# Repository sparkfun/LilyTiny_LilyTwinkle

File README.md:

LilyTiny / LilyTwinkle
======================

[  
*LilyTiny (DEV-10899)*](https://www.sparkfun.com/products/10899) / [*LilyTwinkle (DEV-11364)*](https://www.sparkfun.com/products/11364)

LilyTiny and LilyTwinkle are ATtiny85-based development boards for eTextiles applications. Due to the small size of the board and hardware limitations of the processor, they do not have a bootloader like a conventional LilyPad Arduino compatible does. Instead, six pads are available in the center of the back side of the board, allowing it to be reprogrammed with a standard AVR ISP programmer simply by inserting male headers into the end of the programming cable and pressing them against the board.

In order to write new code for the ATtiny you will need to add support to the Arduino IDE. Please refer to the High-Low Tech group at MIT for a great tutorial on doing this: [http://hlt.media.mit.edu/?p=1695](http://hlt.media.mit.edu/?p=1695)

Repository Contents
-------------------

* **/Firmware** - Separate firmware files for the LilyTiny and the LilyTwinkle.
* **/Fritzing** - Fritzing Example wiring images
* **/Hardware** - All hardware files for both the LilyTiny *and* the LilyTwinkle (they are identical boards). For simplicity's sake, the hardware files are named *LilyTiny*.
* **/Production** - Test bed files and production panel files

Documentation
--------------

* Getting Started Tutorials
  * **[LDK Experiment 6: Microcontroller Circuits](https://learn.sparkfun.com/tutorials/ldk-experiment-6-microcontroller-circuits)**
  * **[Using the LilyPad LilyTwinkle board](https://www.sparkfun.com/tutorials/390)**
* Project Tutorials
  * **[Twinkle Zodiac Constellation](https://learn.sparkfun.com/tutorials/twinkle-zodiac-constellation)**
  * **[Night Sky Halloween Costume](https://learn.sparkfun.com/tutorials/night-sky-halloween-costume)**
  * **[Firefly Jar Assembly Guide](https://learn.sparkfun.com/tutorials/firefly-jar-assembly-guide)** 
  * **[Soft Circuits: LED Feelings Pizza](https://learn.sparkfun.com/tutorials/soft-circuits-led-feelings-pizza)**
  * **[Twinkling Trick or Treat Bag](https://learn.sparkfun.com/tutorials/twinkling-trick-or-treat-bag)**
  * **[Light Up Pennant with E-Textiles](https://learn.sparkfun.com/tutorials/light-up-pennant-with-e-textiles)**
  * **[LilyTiny Plush Monster](https://learn.sparkfun.com/tutorials/lilytiny-plush-monster)**
  * **[Twinkling Fairy Wings](https://www.sparkfun.com/tutorials/396)**
* **[Tiny AVR Programmer Hookup Guide](https://learn.sparkfun.com/tutorials/tiny-avr-programmer-hookup-guide)** - Hookup guide to reprogram an ATtiny85.
* **[Re-Programming the LilyTiny / LilyTwinkle](https://learn.sparkfun.com/tutorials/re-programming-the-lilytiny--lilytwinkle)** - Tutorial to reprogram the LilyTiny or LilyTwinkle.
* **[Quick Reference Guide for ATTiny85](https://learn.sparkfun.com/resources/96)** 

License Information
-------------------
The hardware is released under [Creative Commons ShareAlike 4.0 International](https://creativecommons.org/licenses/by-sa/4.0/).
The code is beerware; if you see me (or any other SparkFun employee) at the local, and you've found our code helpful, please buy us a round!

Distributed as-is; no warranty is given.

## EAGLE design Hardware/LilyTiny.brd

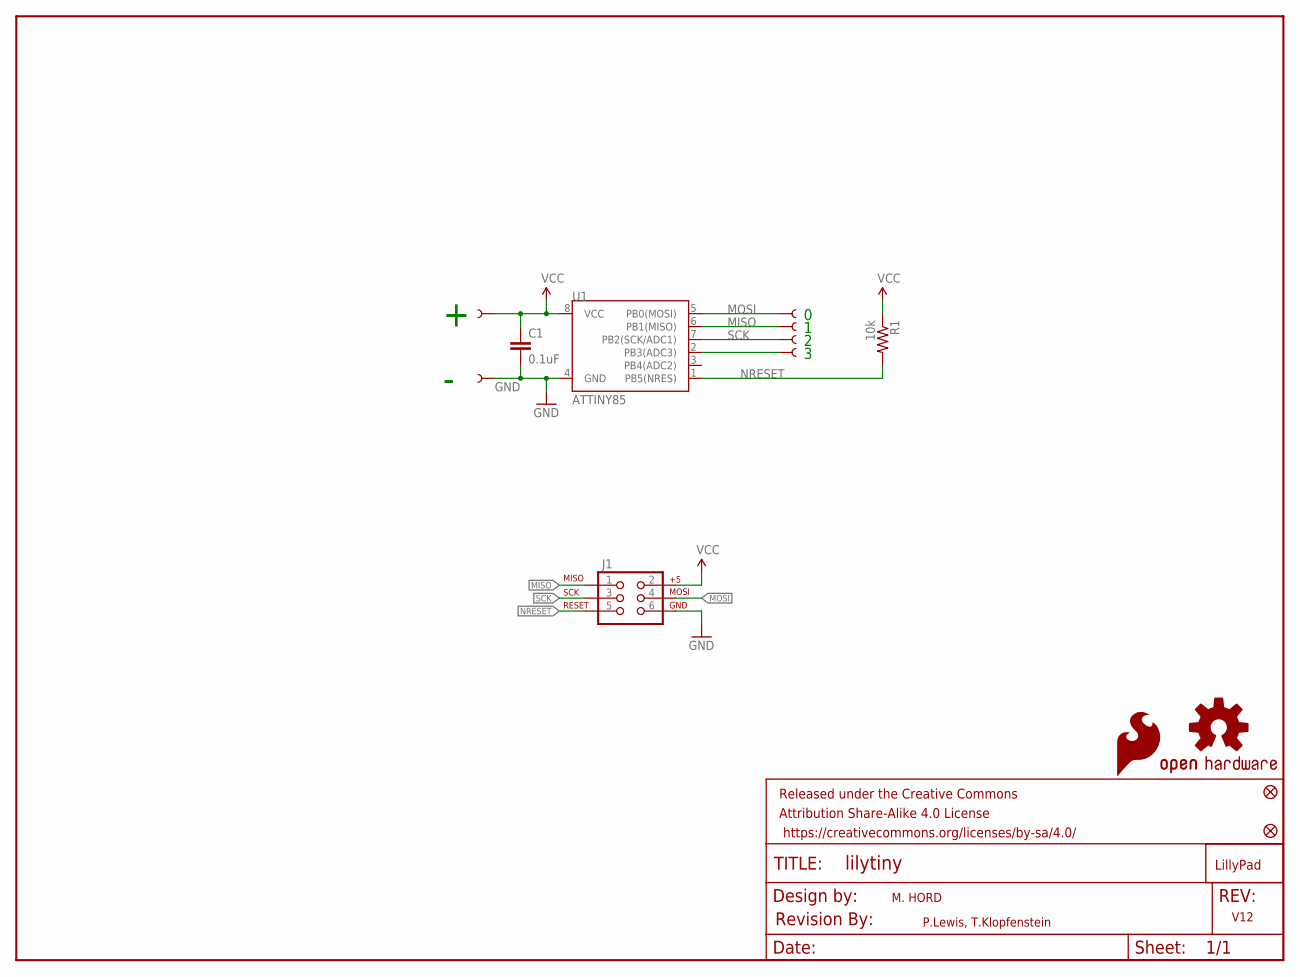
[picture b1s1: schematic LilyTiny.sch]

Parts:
C1: 0.1uF; 0603-CAP
FID1, FID2: FIDUCIAL1X2; FIDUCIAL-1X2
FRAME2: FRAME-LETTER; CREATIVE_COMMONS
J1: AVR_SPI_PRG_6TESTPOINTS; 2X3_TEST_POINTS
LOGO1: OSHW-LOGOS; OSHW-LOGO-S
LOGO2: SFE_LOGO_FLAME.1_INCH; SFE_LOGO_FLAME_.1
R1: 10k; 0603-RES
U1: ATTINY85; SO08-EIAJ
U$1: REVISION
U$2, U$3, U$4, U$5, U$6, U$7: SEWTAP6; PETAL-SMALL-2SIDE
U$8: LOGO-LPL; LOGO-L

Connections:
GND: C1.2, J1.6, U1.4 (GND), U$2.1
MISO: J1.1, U1.6 (PB1(MISO)), U$3.1
MOSI: J1.4, U1.5 (PB0(MOSI)), U$7.1
unnamed: U1.2 (PB3(ADC3)), U$6.1
NRESET: J1.5, R1.2, U1.1 (PB5(NRES))
SCK: J1.3, U1.7 (PB2(SCK/ADC1)), U$4.1
VCC: C1.1, J1.2, R1.1, U1.8 (VCC), U$5.1

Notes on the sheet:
M. HORD
P.Lewis, T.Klopfenstein
V12

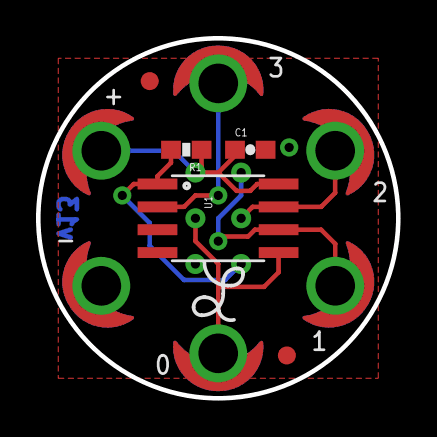
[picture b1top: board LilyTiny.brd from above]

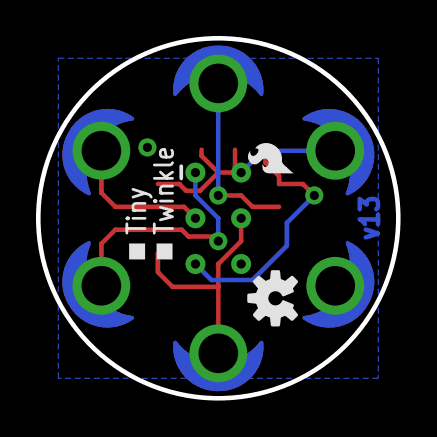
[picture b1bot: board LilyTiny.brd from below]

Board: 2 copper layers, 20.0 x 20.0 mm, 17 parts (3 on the bottom side), 7 nets.

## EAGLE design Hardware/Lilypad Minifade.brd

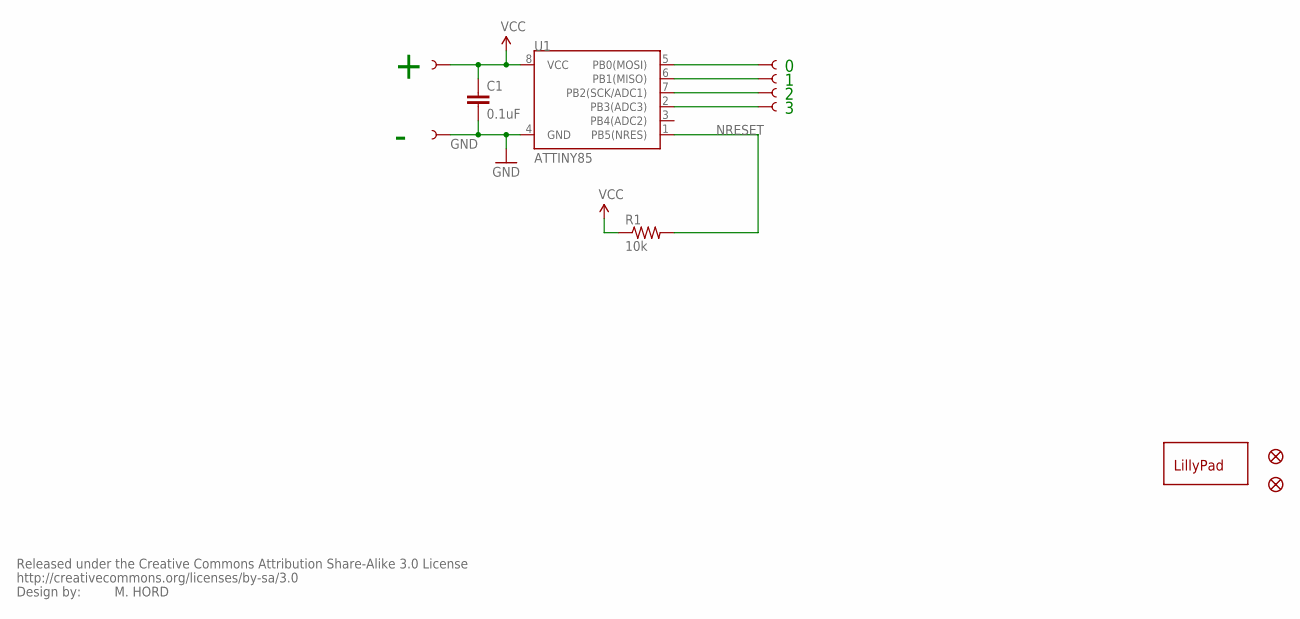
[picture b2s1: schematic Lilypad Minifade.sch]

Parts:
C1: 0.1uF; 0402-CAP
JP1, JP2: FIDUCIALUFIDUCIAL; MICRO-FIDUCIAL
R1: 10k; 0402-RES
U1: ATTINY85; SO08-EIAJ
U$1: CREATIVE_COMMONS
U$2, U$3, U$4, U$5, U$6, U$7: SEWTAP6; PETAL-SMALL-2SIDE
U$8: LOGO-LPL; LOGO-L

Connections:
GND: C1.2, U1.4 (GND), U$2.1
unnamed: U1.5 (PB0(MOSI)), U$7.1
unnamed: U1.6 (PB1(MISO)), U$3.1
unnamed: U1.7 (PB2(SCK/ADC1)), U$4.1
unnamed: U1.2 (PB3(ADC3)), U$6.1
NRESET: R1.2, U1.1 (PB5(NRES))
VCC: C1.1, R1.1, U1.8 (VCC), U$5.1

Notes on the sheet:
M. HORD

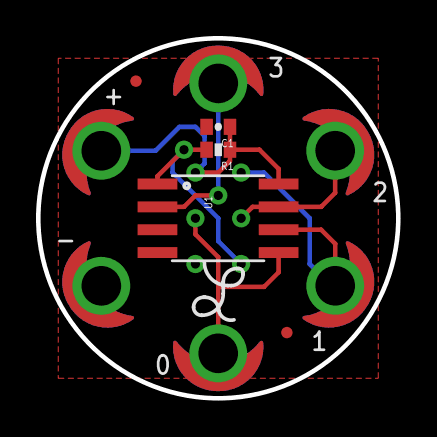
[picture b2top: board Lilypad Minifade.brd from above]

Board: 2 copper layers, 20.0 x 20.0 mm, 13 parts (0 on the bottom side), 7 nets.

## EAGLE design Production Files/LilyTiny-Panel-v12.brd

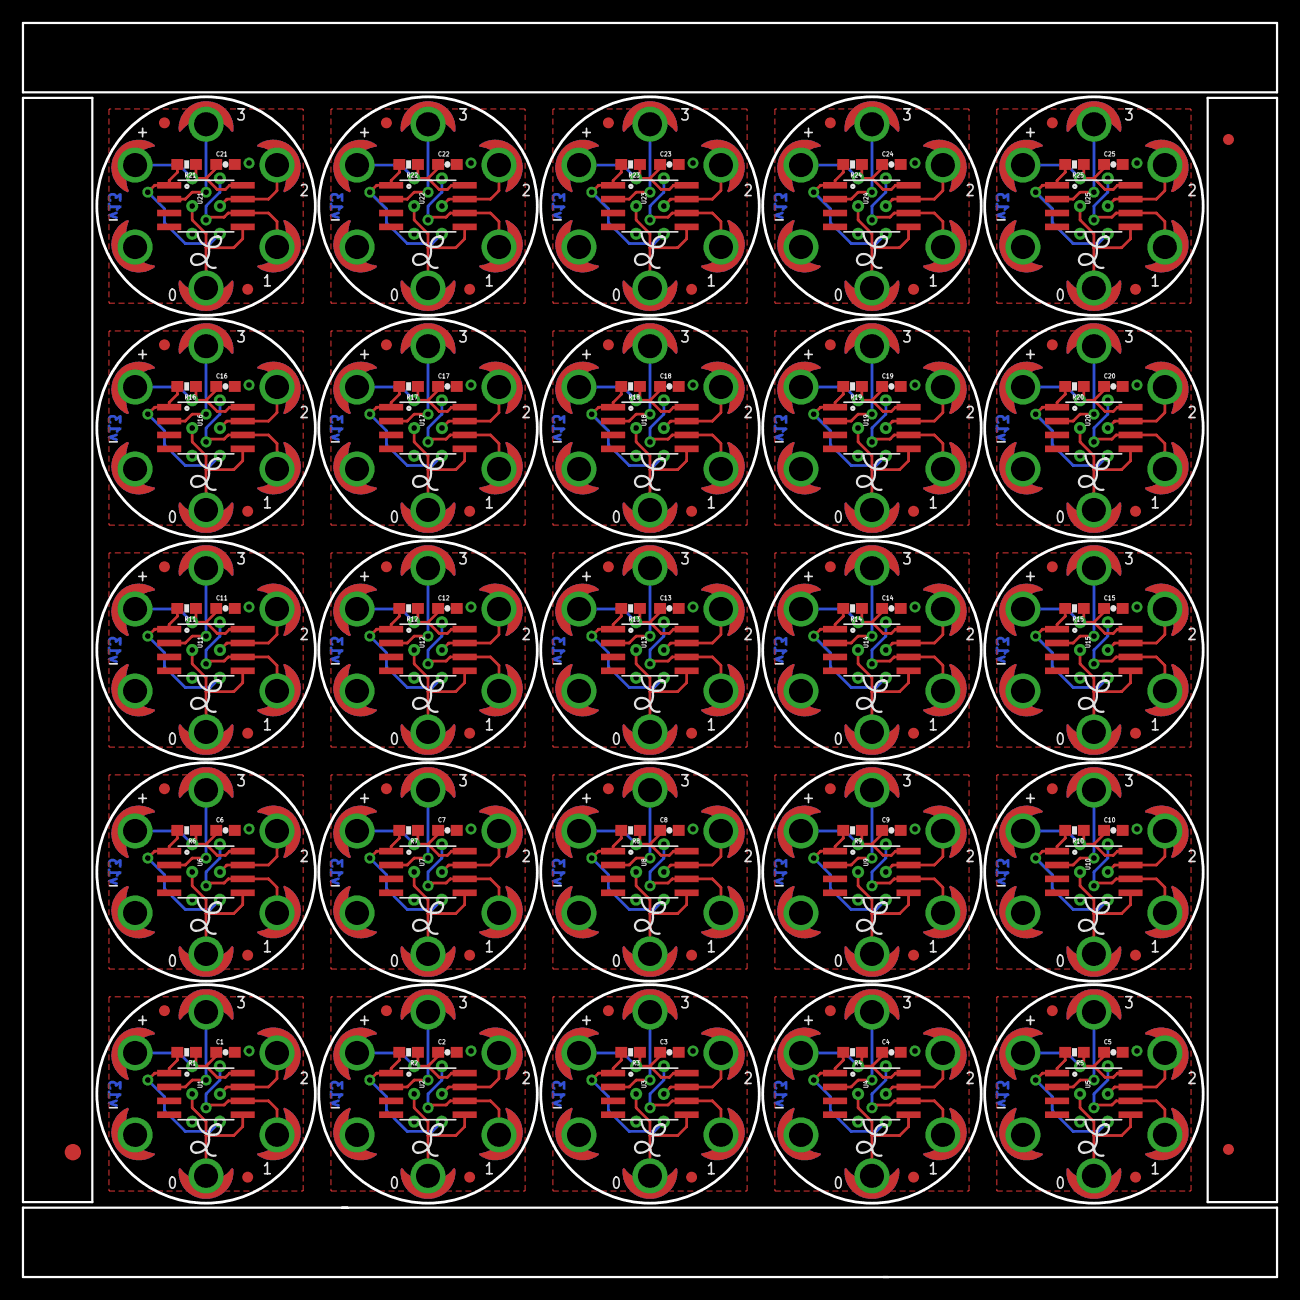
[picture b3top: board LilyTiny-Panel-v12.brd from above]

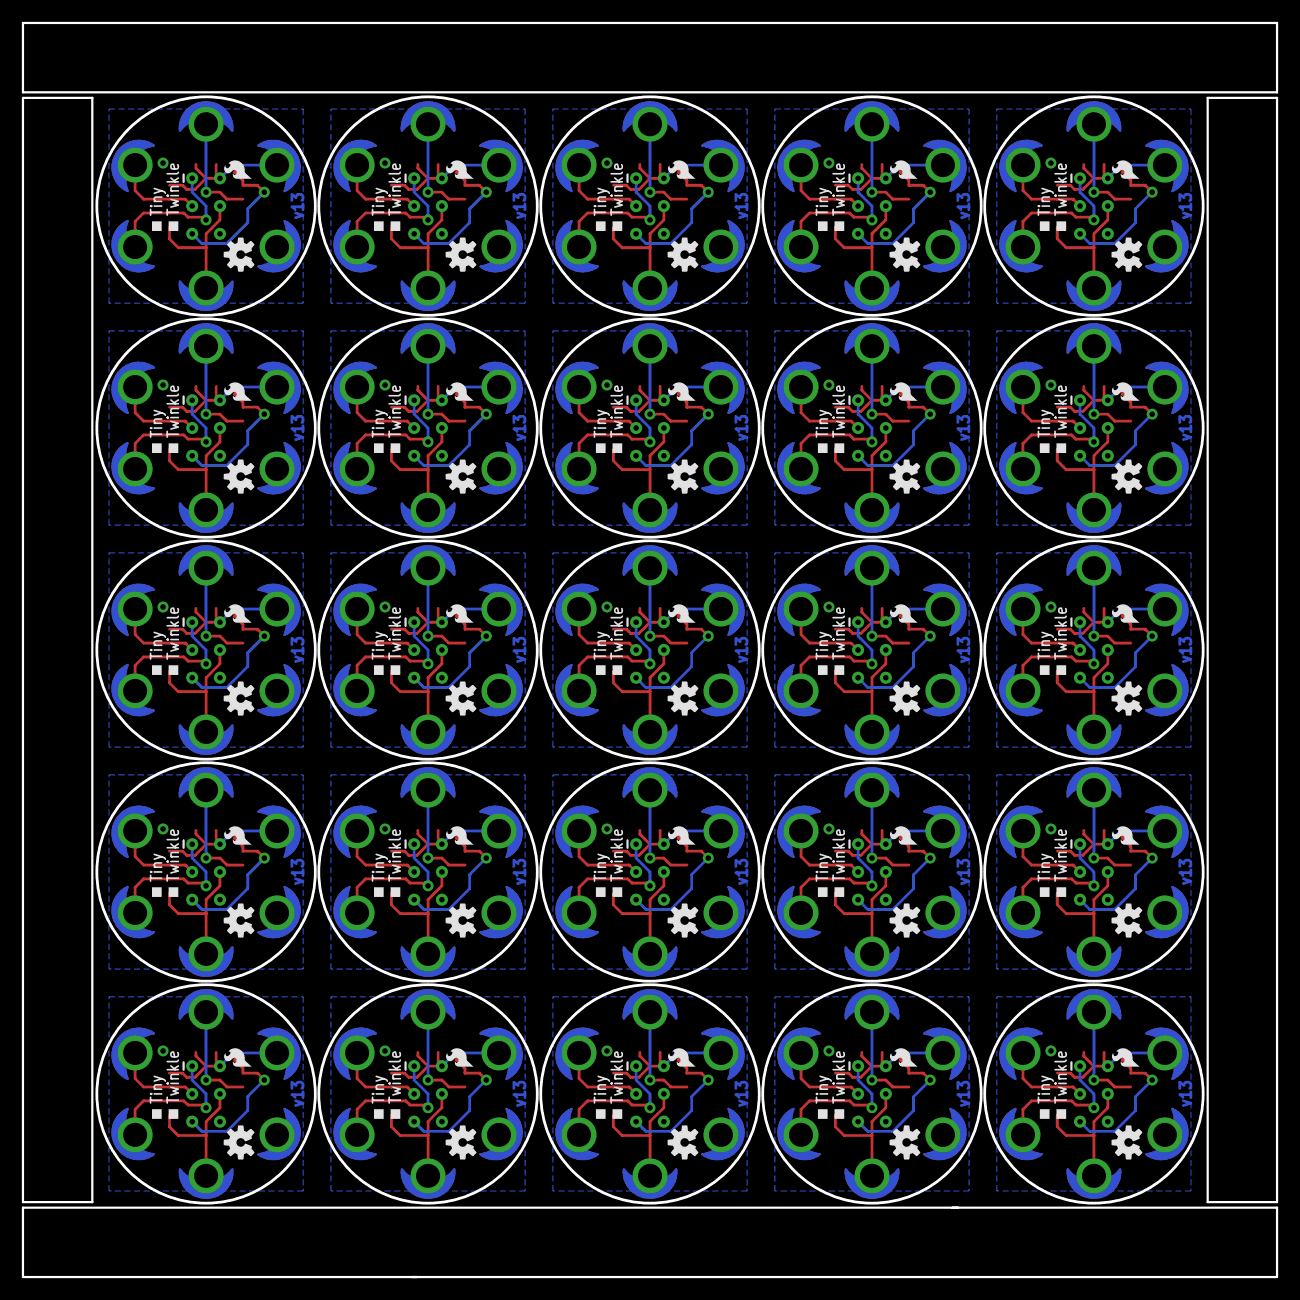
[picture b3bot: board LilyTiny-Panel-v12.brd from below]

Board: 2 copper layers, 114.8 x 114.8 mm, 378 parts (75 on the bottom side), 175 nets.

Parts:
C1, C2, C3, C4, C5, C6, C7, C8, C9, C10, C11, C12, C13, C14, C15, C16, C17, C18, C19, C20, C21, C22, C23, C24, C25: 0.1uF; 0603-CAP
E$1: FIDUCIAL-1.5X3
E$4, E$6: FIDUCIAL-1X2
FID1, FID2, FID3, FID4, FID5, FID6, FID7, FID8, FID9, FID10, FID11, FID12, FID13, FID14, FID15, FID16, FID17, FID18, FID19, FID20, FID21, FID22, FID23, FID24, FID25, FID26, FID27, FID28, FID29, FID30, FID31, FID32, FID33, FID34, FID35, FID36, FID37, FID38, FID39, FID40, FID41, FID42, FID43, FID44, FID45, FID46, FID47, FID48, FID49, FID50: FIDUCIAL1X2; FIDUCIAL-1X2
J1, J2, J3, J4, J5, J6, J7, J8, J9, J10, J11, J12, J13, J14, J15, J16, J17, J18, J19, J20, J21, J22, J23, J24, J25: 2X3_TEST_POINTS
LOGO1, LOGO3, LOGO5, LOGO7, LOGO9, LOGO11, LOGO13, LOGO15, LOGO17, LOGO19, LOGO21, LOGO23, LOGO25, LOGO27, LOGO29, LOGO31, LOGO33, LOGO35, LOGO37, LOGO39, LOGO41, LOGO43, LOGO45, LOGO47, LOGO49: OSHW-LOGOS; OSHW-LOGO-S
LOGO2, LOGO4, LOGO6, LOGO8, LOGO10, LOGO12, LOGO14, LOGO16, LOGO18, LOGO20, LOGO22, LOGO24, LOGO26, LOGO28, LOGO30, LOGO32, LOGO34, LOGO36, LOGO38, LOGO40, LOGO42, LOGO44, LOGO46, LOGO48, LOGO50: SFE_LOGO_FLAME.1_INCH; SFE_LOGO_FLAME_.1
R1, R2, R3, R4, R5, R6, R7, R8, R9, R10, R11, R12, R13, R14, R15, R16, R17, R18, R19, R20, R21, R22, R23, R24, R25: 10k; 0603-RES
U1, U2, U3, U4, U5, U6, U7, U8, U9, U10, U11, U12, U13, U14, U15, U16, U17, U18, U19, U20, U21, U22, U23, U24, U25: ATTINY85; SO08-EIAJ
U$1, U$2, U$3, U$4, U$5, U$6, U$7, U$9, U$10, U$11, U$12, U$13, U$15, U$16, U$17, U$18, U$19, U$20, U$22, U$23, U$24, U$25, U$26, U$27, U$29, U$30, U$31, U$32, U$33, U$34, U$36, U$37, U$38, U$39, U$40, U$41, U$43, U$44, U$45, U$46, U$47, U$48, U$50, U$51, U$52, U$53, U$54, U$55, U$57, U$58, U$59, U$60, U$61, U$62, U$64, U$65, U$66, U$67, U$68, U$69, U$71, U$72, U$73, U$74, U$75, U$76, U$78, U$79, U$80, U$81, U$82, U$83, U$85, U$86, U$87, U$88, U$89, U$90, U$92, U$93, U$94, U$95, U$96, U$97, U$99, U$100, U$101, U$102, U$103, U$104, U$106, U$107, U$108, U$109, U$110, U$111, U$113, U$114, U$115, U$116, U$117, U$118, U$120, U$121, U$122, U$123, U$124, U$125, U$127, U$128, U$129, U$130, U$131, U$132, U$134, U$135, U$136, U$137, U$138, U$139, U$141, U$142, U$143, U$144, U$145, U$146, U$148, U$149, U$150, U$151, U$152, U$153, U$155, U$156, U$157, U$158, U$159, U$160, U$162, U$163, U$164, U$165, U$166, U$167, U$169, U$170, U$171, U$172, U$173, U$174: SEWTAP6; PETAL-SMALL-2SIDE
U$8, U$14, U$21, U$28, U$35, U$42, U$49, U$56, U$63, U$70, U$77, U$84, U$91, U$98, U$105, U$112, U$119, U$126, U$133, U$140, U$147, U$154, U$161, U$168, U$175: LOGO-LPL; LOGO-L

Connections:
GND: C1.2, J1.6, U1.4, U$2.1
GND1: C2.2, J2.6, U2.4, U$1.1
GND2: C3.2, J3.6, U3.4, U$15.1
GND3: C4.2, J4.6, U4.4, U$22.1
GND4: C5.2, J5.6, U5.4, U$29.1
GND5: C6.2, J6.6, U6.4, U$36.1
GND6: C7.2, J7.6, U7.4, U$43.1
GND7: C8.2, J8.6, U8.4, U$50.1
GND8: C9.2, J9.6, U9.4, U$57.1
GND9: C10.2, J10.6, U10.4, U$64.1
GND10: C11.2, J11.6, U11.4, U$71.1
GND11: C12.2, J12.6, U12.4, U$78.1
GND12: C13.2, J13.6, U13.4, U$85.1
GND13: C14.2, J14.6, U14.4, U$92.1
GND14: C15.2, J15.6, U15.4, U$99.1
GND15: C16.2, J16.6, U16.4, U$106.1
GND16: C17.2, J17.6, U17.4, U$113.1
GND17: C18.2, J18.6, U18.4, U$120.1
GND18: C19.2, J19.6, U19.4, U$127.1
GND19: C20.2, J20.6, U20.4, U$134.1
GND20: C21.2, J21.6, U21.4, U$141.1
GND21: C22.2, J22.6, U22.4, U$148.1
GND22: C23.2, J23.6, U23.4, U$155.1
GND23: C24.2, J24.6, U24.4, U$162.1
GND24: C25.2, J25.6, U25.4, U$169.1
MISO: J1.1, U1.6, U$3.1
MISO1: J2.1, U2.6, U$9.1
MISO2: J3.1, U3.6, U$16.1
MISO3: J4.1, U4.6, U$23.1
MISO4: J5.1, U5.6, U$30.1
MISO5: J6.1, U6.6, U$37.1
MISO6: J7.1, U7.6, U$44.1
MISO7: J8.1, U8.6, U$51.1
MISO8: J9.1, U9.6, U$58.1
MISO9: J10.1, U10.6, U$65.1
MISO10: J11.1, U11.6, U$72.1
MISO11: J12.1, U12.6, U$79.1
MISO12: J13.1, U13.6, U$86.1
MISO13: J14.1, U14.6, U$93.1
MISO14: J15.1, U15.6, U$100.1
MISO15: J16.1, U16.6, U$107.1
MISO16: J17.1, U17.6, U$114.1
MISO17: J18.1, U18.6, U$121.1
MISO18: J19.1, U19.6, U$128.1
MISO19: J20.1, U20.6, U$135.1
MISO20: J21.1, U21.6, U$142.1
MISO21: J22.1, U22.6, U$149.1
MISO22: J23.1, U23.6, U$156.1
MISO23: J24.1, U24.6, U$163.1
MISO24: J25.1, U25.6, U$170.1
MOSI: J1.4, U1.5, U$7.1
MOSI1: J2.4, U2.5, U$13.1
MOSI2: J3.4, U3.5, U$20.1
MOSI3: J4.4, U4.5, U$27.1
MOSI4: J5.4, U5.5, U$34.1
MOSI5: J6.4, U6.5, U$41.1
MOSI6: J7.4, U7.5, U$48.1
MOSI7: J8.4, U8.5, U$55.1
MOSI8: J9.4, U9.5, U$62.1
MOSI9: J10.4, U10.5, U$69.1
MOSI10: J11.4, U11.5, U$76.1
MOSI11: J12.4, U12.5, U$83.1
MOSI12: J13.4, U13.5, U$90.1
MOSI13: J14.4, U14.5, U$97.1
MOSI14: J15.4, U15.5, U$104.1
MOSI15: J16.4, U16.5, U$111.1
MOSI16: J17.4, U17.5, U$118.1
MOSI17: J18.4, U18.5, U$125.1
MOSI18: J19.4, U19.5, U$132.1
MOSI19: J20.4, U20.5, U$139.1
MOSI20: J21.4, U21.5, U$146.1
MOSI21: J22.4, U22.5, U$153.1
MOSI22: J23.4, U23.5, U$160.1
MOSI23: J24.4, U24.5, U$167.1
MOSI24: J25.4, U25.5, U$174.1
unnamed: U2.2, U$12.1
unnamed: U3.2, U$19.1
unnamed: U4.2, U$26.1
unnamed: U5.2, U$33.1
unnamed: U1.2, U$6.1
unnamed: U6.2, U$40.1
unnamed: U7.2, U$47.1
unnamed: U8.2, U$54.1
unnamed: U9.2, U$61.1
unnamed: U10.2, U$68.1
unnamed: U11.2, U$75.1
unnamed: U12.2, U$82.1
unnamed: U13.2, U$89.1
unnamed: U14.2, U$96.1
unnamed: U15.2, U$103.1
unnamed: U16.2, U$110.1
unnamed: U17.2, U$117.1
unnamed: U18.2, U$124.1
unnamed: U19.2, U$131.1
unnamed: U20.2, U$138.1
unnamed: U21.2, U$145.1
unnamed: U22.2, U$152.1
unnamed: U23.2, U$159.1
unnamed: U24.2, U$166.1
unnamed: U25.2, U$173.1
NRESET: J1.5, R1.2, U1.1
NRESET1: J2.5, R2.2, U2.1
NRESET2: J3.5, R3.2, U3.1
NRESET3: J4.5, R4.2, U4.1
NRESET4: J5.5, R5.2, U5.1
NRESET5: J6.5, R6.2, U6.1
NRESET6: J7.5, R7.2, U7.1
NRESET7: J8.5, R8.2, U8.1
NRESET8: J9.5, R9.2, U9.1
NRESET9: J10.5, R10.2, U10.1
NRESET10: J11.5, R11.2, U11.1
NRESET11: J12.5, R12.2, U12.1
NRESET12: J13.5, R13.2, U13.1
NRESET13: J14.5, R14.2, U14.1
NRESET14: J15.5, R15.2, U15.1
NRESET15: J16.5, R16.2, U16.1
NRESET16: J17.5, R17.2, U17.1
NRESET17: J18.5, R18.2, U18.1
NRESET18: J19.5, R19.2, U19.1
NRESET19: J20.5, R20.2, U20.1
NRESET20: J21.5, R21.2, U21.1
NRESET21: J22.5, R22.2, U22.1
NRESET22: J23.5, R23.2, U23.1
NRESET23: J24.5, R24.2, U24.1
NRESET24: J25.5, R25.2, U25.1
SCK: J1.3, U1.7, U$4.1
SCK1: J2.3, U2.7, U$10.1
SCK2: J3.3, U3.7, U$17.1
SCK3: J4.3, U4.7, U$24.1
SCK4: J5.3, U5.7, U$31.1
SCK5: J6.3, U6.7, U$38.1
SCK6: J7.3, U7.7, U$45.1
SCK7: J8.3, U8.7, U$52.1
SCK8: J9.3, U9.7, U$59.1
SCK9: J10.3, U10.7, U$66.1
SCK10: J11.3, U11.7, U$73.1
SCK11: J12.3, U12.7, U$80.1
SCK12: J13.3, U13.7, U$87.1
SCK13: J14.3, U14.7, U$94.1
SCK14: J15.3, U15.7, U$101.1
SCK15: J16.3, U16.7, U$108.1
SCK16: J17.3, U17.7, U$115.1
SCK17: J18.3, U18.7, U$122.1
SCK18: J19.3, U19.7, U$129.1
SCK19: J20.3, U20.7, U$136.1
SCK20: J21.3, U21.7, U$143.1
SCK21: J22.3, U22.7, U$150.1
SCK22: J23.3, U23.7, U$157.1
SCK23: J24.3, U24.7, U$164.1
SCK24: J25.3, U25.7, U$171.1
VCC: C1.1, J1.2, R1.1, U1.8, U$5.1
VCC1: C2.1, J2.2, R2.1, U2.8, U$11.1
VCC2: C3.1, J3.2, R3.1, U3.8, U$18.1
VCC3: C4.1, J4.2, R4.1, U4.8, U$25.1
VCC4: C5.1, J5.2, R5.1, U5.8, U$32.1
VCC5: C6.1, J6.2, R6.1, U6.8, U$39.1
VCC6: C7.1, J7.2, R7.1, U7.8, U$46.1
VCC7: C8.1, J8.2, R8.1, U8.8, U$53.1
VCC8: C9.1, J9.2, R9.1, U9.8, U$60.1
VCC9: C10.1, J10.2, R10.1, U10.8, U$67.1
VCC10: C11.1, J11.2, R11.1, U11.8, U$74.1
VCC11: C12.1, J12.2, R12.1, U12.8, U$81.1
VCC12: C13.1, J13.2, R13.1, U13.8, U$88.1
VCC13: C14.1, J14.2, R14.1, U14.8, U$95.1
VCC14: C15.1, J15.2, R15.1, U15.8, U$102.1
VCC15: C16.1, J16.2, R16.1, U16.8, U$109.1
VCC16: C17.1, J17.2, R17.1, U17.8, U$116.1
VCC17: C18.1, J18.2, R18.1, U18.8, U$123.1
VCC18: C19.1, J19.2, R19.1, U19.8, U$130.1
VCC19: C20.1, J20.2, R20.1, U20.8, U$137.1
VCC20: C21.1, J21.2, R21.1, U21.8, U$144.1
VCC21: C22.1, J22.2, R22.1, U22.8, U$151.1
VCC22: C23.1, J23.2, R23.1, U23.8, U$158.1
VCC23: C24.1, J24.2, R24.1, U24.8, U$165.1
VCC24: C25.1, J25.2, R25.1, U25.8, U$172.1

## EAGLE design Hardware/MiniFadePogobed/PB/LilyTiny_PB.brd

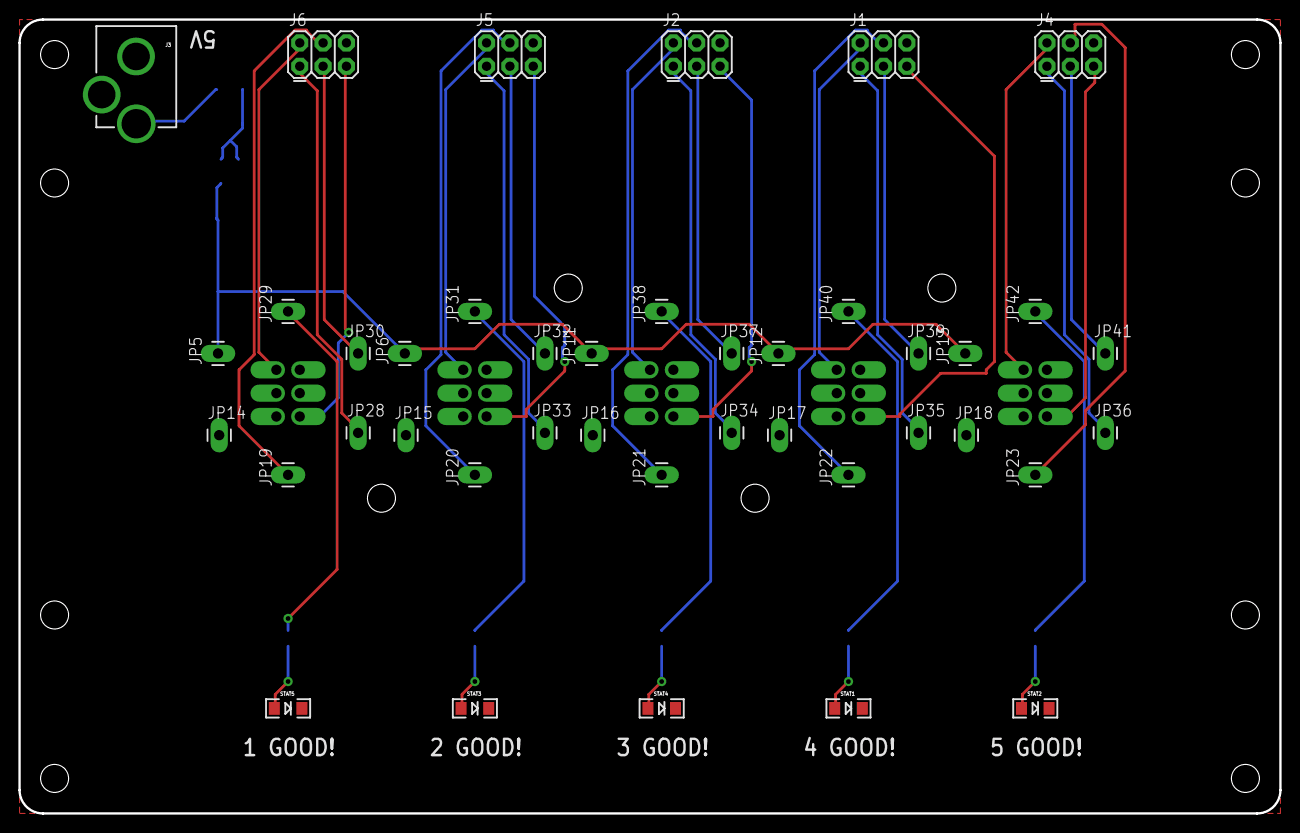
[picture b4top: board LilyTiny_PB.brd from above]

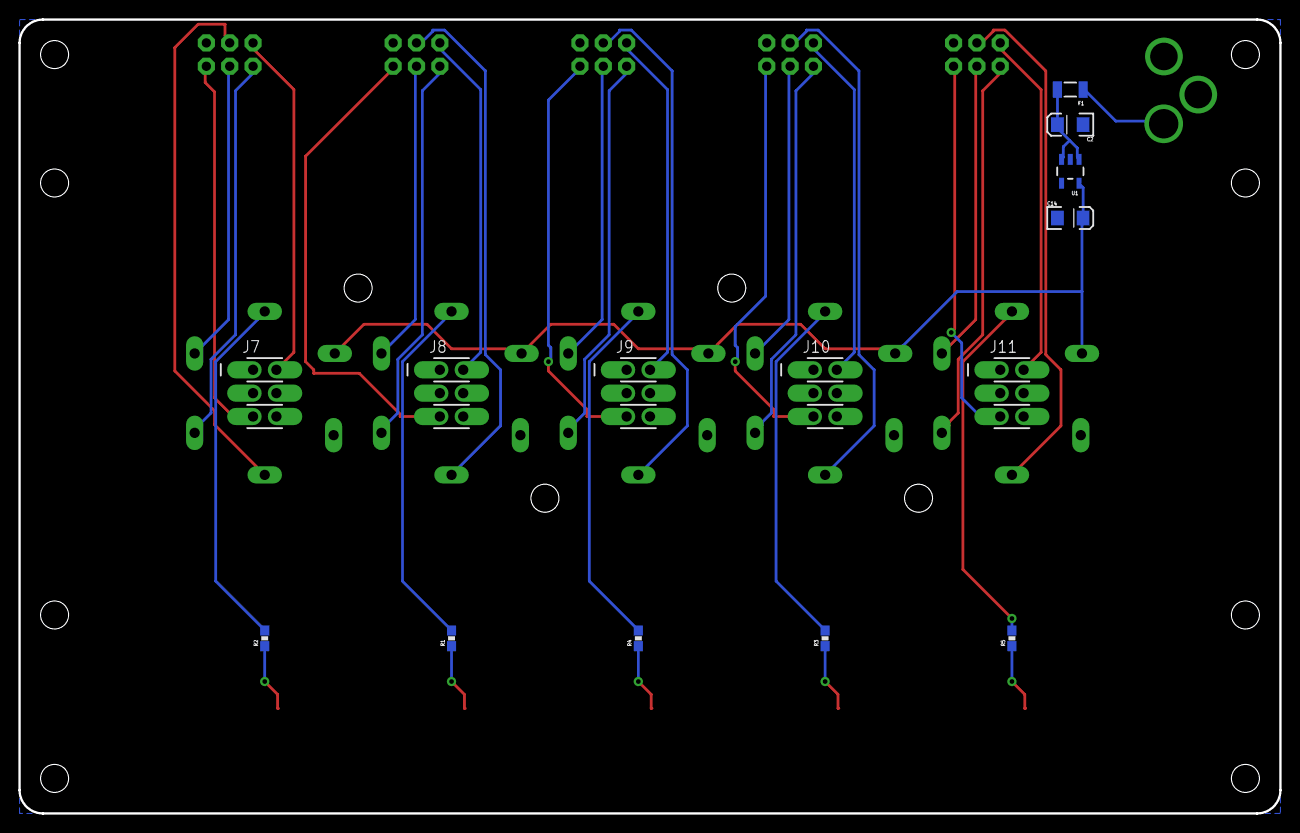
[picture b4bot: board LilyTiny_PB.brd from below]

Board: 2 copper layers, 137.2 x 86.4 mm, 67 parts (14 on the bottom side), 39 nets.

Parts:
C2, C14: 10uF; EIA3216
F1: PTCSMD; PTC-1206
J1, J2, J4, J5, J6: AVR_SPI_PRG_6PTH; 2X3
J3: 7V; POWER_JACK_PTH_LOCK
J7, J8, J9, J10, J11: AVR_SPI_PRG_6OFFSET_PADS; 2X3_OFFSET
JP1, JP2, JP3, JP4, JP7, JP8, JP9, JP10, JP24, JP25, JP26, JP27: STAND-OFFTIGHT; STAND-OFF-TIGHT
JP5, JP6, JP11, JP12, JP13, JP14, JP15, JP16, JP17, JP18, JP19, JP20, JP21, JP22, JP23, JP28, JP29, JP30, JP31, JP32, JP33, JP34, JP35, JP36, JP37, JP38, JP39, JP40, JP41, JP42: M01PTH_LONGPAD; 1X01_LONGPAD
R1, R2, R3, R4, R5: 330; 0603-RES
STAT1, STAT2, STAT3, STAT4, STAT5: Yellow; LED-1206
U1: 3.3V; SOT23-5

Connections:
A31: JP29.1, R5.2
A32: JP31.1, R3.2
A33: JP38.1, R4.2
A34: JP40.1, R1.2
A35: JP42.1, R2.2
GND: C2.C, C14.C, J1.6, J2.6, J3.GND, J3.GNDBREAK, J4.6, J5.6, J6.6, J7.6, J8.6, J9.6, J10.6, J11.6, JP14.1, JP15.1, JP16.1, JP17.1, JP18.1, STAT1.C, STAT2.C, STAT3.C, STAT4.C, STAT5.C, U1.2
MISO1: J6.1, JP28.1
MISO2: J5.1, JP33.1
MISO3: J2.1, JP34.1
MISO4: J1.1, JP35.1
MISO5: J4.1, JP36.1
MOSI1: J6.4, JP19.1
MOSI2: J5.4, JP20.1
MOSI3: J2.4, JP21.1
MOSI4: J1.4, JP22.1
MOSI5: J4.4, JP23.1
unnamed: R1.1, STAT1.A
unnamed: R2.1, STAT2.A
unnamed: R3.1, STAT3.A
unnamed: C2.A, F1.2, U1.1, U1.3
unnamed: R4.1, STAT4.A
unnamed: R5.1, STAT5.A
RAW: F1.1, J3.PWR
RST1: J6.5, J11.5
RST2: J5.5, J10.5
RST3: J2.5, J9.5
RST4: J1.5, J8.5
RST5: J4.5, J7.5
SCK1: J6.3, JP30.1
SCK2: J5.3, JP32.1
SCK3: J2.3, JP37.1
SCK4: J1.3, JP39.1
SCK5: J4.3, JP41.1
VCC: C14.A, JP5.1, JP6.1, JP11.1, JP12.1, JP13.1, U1.5
VCC1: J6.2, J11.2
VCC2: J5.2, J10.2
VCC3: J2.2, J9.2
VCC4: J1.2, J8.2
VCC5: J4.2, J7.2

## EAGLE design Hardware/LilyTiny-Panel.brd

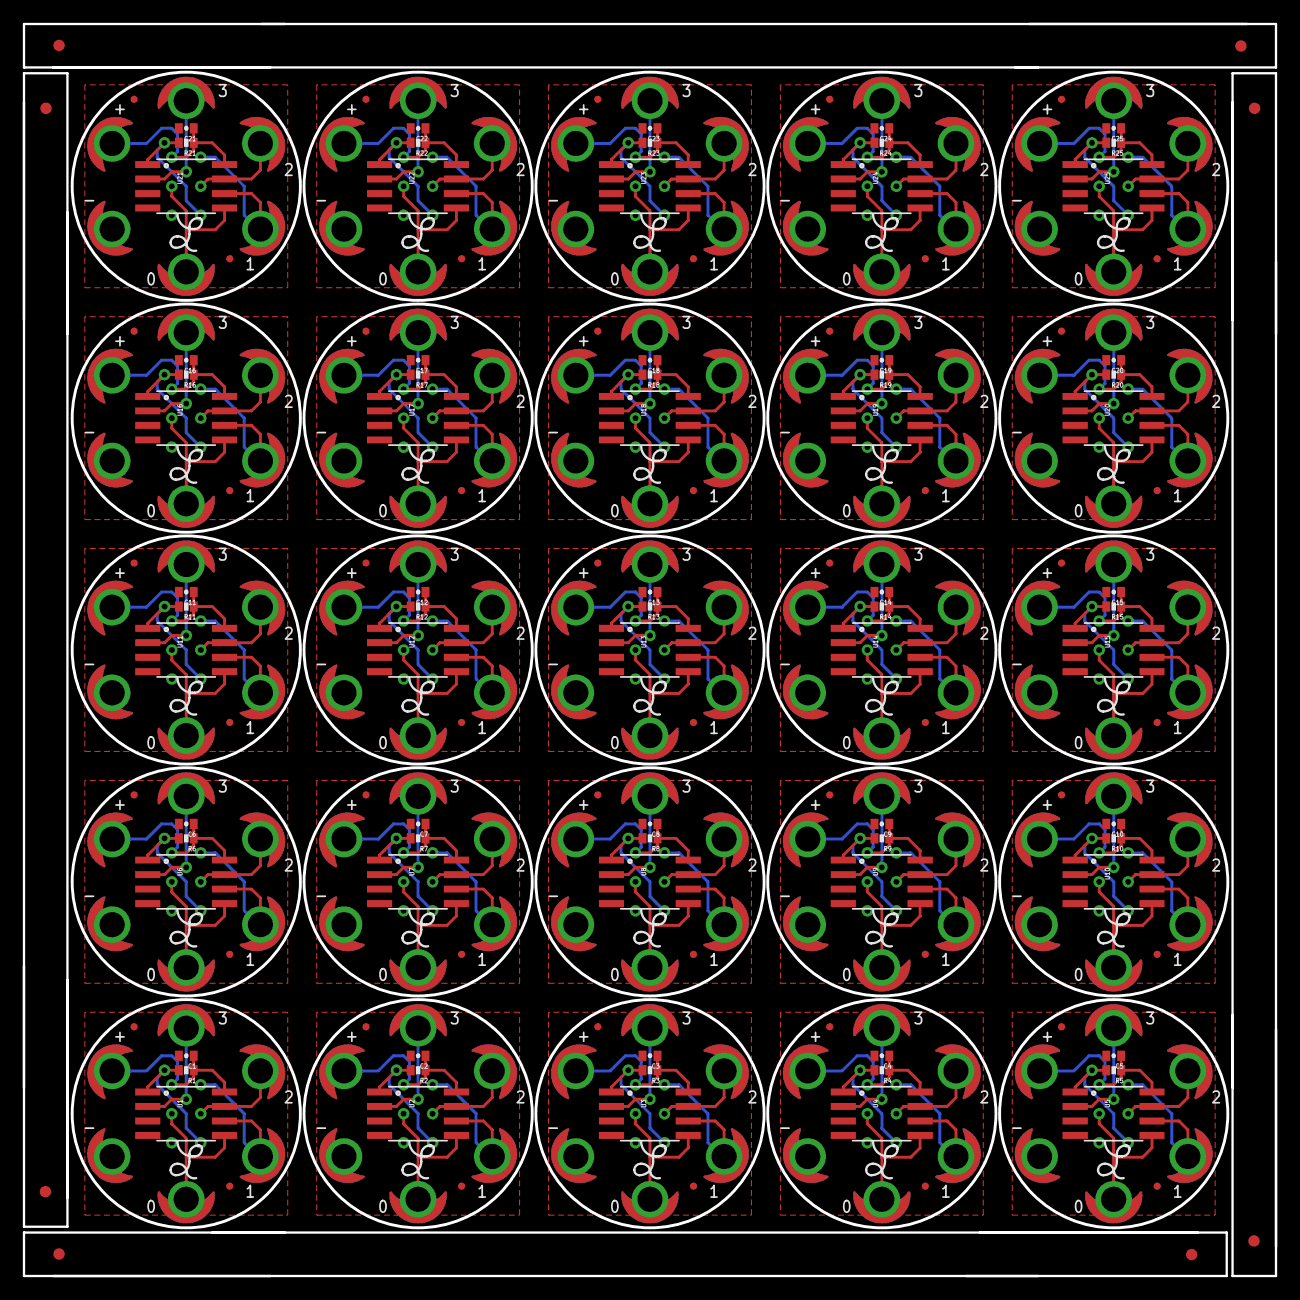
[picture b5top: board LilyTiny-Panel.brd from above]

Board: 2 copper layers, 109.7 x 109.7 mm, 308 parts (0 on the bottom side), 175 nets.

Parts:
C1, C2, C3, C4, C5, C6, C7, C8, C9, C10, C11, C12, C13, C14, C15, C16, C17, C18, C19, C20, C21, C22, C23, C24, C25: 0.1uF; 0402-CAP
E$1, E$2, E$3, E$4, E$5, E$6, E$7, E$8: FIDUCIAL-1X2
JP1, JP2, JP3, JP4, JP5, JP6, JP7, JP8, JP9, JP10, JP11, JP12, JP13, JP14, JP15, JP16, JP17, JP18, JP19, JP20, JP21, JP22, JP23, JP24, JP25, JP26, JP27, JP28, JP29, JP30, JP31, JP32, JP33, JP34, JP35, JP36, JP37, JP38, JP39, JP40, JP41, JP42, JP43, JP44, JP45, JP46, JP47, JP48, JP49, JP50: FIDUCIALUFIDUCIAL; MICRO-FIDUCIAL
R1, R2, R3, R4, R5, R6, R7, R8, R9, R10, R11, R12, R13, R14, R15, R16, R17, R18, R19, R20, R21, R22, R23, R24, R25: 10k; 0402-RES
U1, U2, U3, U4, U5, U6, U7, U8, U9, U10, U11, U12, U13, U14, U15, U16, U17, U18, U19, U20, U21, U22, U23, U24, U25: ATTINY85; SO08-EIAJ
U$1, U$2, U$3, U$4, U$5, U$6, U$7, U$9, U$10, U$11, U$12, U$13, U$15, U$16, U$17, U$18, U$19, U$20, U$22, U$23, U$24, U$25, U$26, U$27, U$29, U$30, U$31, U$32, U$33, U$34, U$36, U$37, U$38, U$39, U$40, U$41, U$43, U$44, U$45, U$46, U$47, U$48, U$50, U$51, U$52, U$53, U$54, U$55, U$57, U$58, U$59, U$60, U$61, U$62, U$64, U$65, U$66, U$67, U$68, U$69, U$71, U$72, U$73, U$74, U$75, U$76, U$78, U$79, U$80, U$81, U$82, U$83, U$85, U$86, U$87, U$88, U$89, U$90, U$92, U$93, U$94, U$95, U$96, U$97, U$99, U$100, U$101, U$102, U$103, U$104, U$106, U$107, U$108, U$109, U$110, U$111, U$113, U$114, U$115, U$116, U$117, U$118, U$120, U$121, U$122, U$123, U$124, U$125, U$127, U$128, U$129, U$130, U$131, U$132, U$134, U$135, U$136, U$137, U$138, U$139, U$141, U$142, U$143, U$144, U$145, U$146, U$148, U$149, U$150, U$151, U$152, U$153, U$155, U$156, U$157, U$158, U$159, U$160, U$162, U$163, U$164, U$165, U$166, U$167, U$169, U$170, U$171, U$172, U$173, U$174: SEWTAP6; PETAL-SMALL-2SIDE
U$8, U$14, U$21, U$28, U$35, U$42, U$49, U$56, U$63, U$70, U$77, U$84, U$91, U$98, U$105, U$112, U$119, U$126, U$133, U$140, U$147, U$154, U$161, U$168, U$175: LOGO-LPL; LOGO-L

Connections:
GND: C1.2, U1.4, U$2.1
GND1: C2.2, U2.4, U$1.1
GND2: C3.2, U3.4, U$15.1
GND3: C4.2, U4.4, U$22.1
GND4: C5.2, U5.4, U$29.1
GND5: C6.2, U6.4, U$36.1
GND6: C7.2, U7.4, U$43.1
GND7: C8.2, U8.4, U$50.1
GND8: C9.2, U9.4, U$57.1
GND9: C10.2, U10.4, U$64.1
GND10: C11.2, U11.4, U$71.1
GND11: C12.2, U12.4, U$78.1
GND12: C13.2, U13.4, U$85.1
GND13: C14.2, U14.4, U$92.1
GND14: C15.2, U15.4, U$99.1
GND15: C16.2, U16.4, U$106.1
GND16: C17.2, U17.4, U$113.1
GND17: C18.2, U18.4, U$120.1
GND18: C19.2, U19.4, U$127.1
GND19: C20.2, U20.4, U$134.1
GND20: C21.2, U21.4, U$141.1
GND21: C22.2, U22.4, U$148.1
GND22: C23.2, U23.4, U$155.1
GND23: C24.2, U24.4, U$162.1
GND24: C25.2, U25.4, U$169.1
unnamed: U2.5, U$13.1
unnamed: U1.5, U$7.1
unnamed: U1.6, U$3.1
unnamed: U1.7, U$4.1
unnamed: U1.2, U$6.1
unnamed: U2.6, U$9.1
unnamed: U2.7, U$10.1
unnamed: U2.2, U$12.1
unnamed: U3.5, U$20.1
unnamed: U3.6, U$16.1
unnamed: U3.7, U$17.1
unnamed: U3.2, U$19.1
unnamed: U4.5, U$27.1
unnamed: U4.6, U$23.1
unnamed: U4.7, U$24.1
unnamed: U4.2, U$26.1
unnamed: U5.5, U$34.1
unnamed: U5.6, U$30.1
unnamed: U5.7, U$31.1
unnamed: U5.2, U$33.1
unnamed: U6.5, U$41.1
unnamed: U6.6, U$37.1
unnamed: U6.7, U$38.1
unnamed: U6.2, U$40.1
unnamed: U7.5, U$48.1
unnamed: U7.6, U$44.1
unnamed: U7.7, U$45.1
unnamed: U7.2, U$47.1
unnamed: U8.5, U$55.1
unnamed: U8.6, U$51.1
unnamed: U8.7, U$52.1
unnamed: U8.2, U$54.1
unnamed: U9.5, U$62.1
unnamed: U9.6, U$58.1
unnamed: U9.7, U$59.1
unnamed: U9.2, U$61.1
unnamed: U10.5, U$69.1
unnamed: U10.6, U$65.1
unnamed: U10.7, U$66.1
unnamed: U10.2, U$68.1
unnamed: U11.5, U$76.1
unnamed: U11.6, U$72.1
unnamed: U11.7, U$73.1
unnamed: U11.2, U$75.1
unnamed: U12.5, U$83.1
unnamed: U12.6, U$79.1
unnamed: U12.7, U$80.1
unnamed: U12.2, U$82.1
unnamed: U13.5, U$90.1
unnamed: U13.6, U$86.1
unnamed: U13.7, U$87.1
unnamed: U13.2, U$89.1
unnamed: U14.5, U$97.1
unnamed: U14.6, U$93.1
unnamed: U14.7, U$94.1
unnamed: U14.2, U$96.1
unnamed: U15.5, U$104.1
unnamed: U15.6, U$100.1
unnamed: U15.7, U$101.1
unnamed: U15.2, U$103.1
unnamed: U16.5, U$111.1
unnamed: U16.6, U$107.1
unnamed: U16.7, U$108.1
unnamed: U16.2, U$110.1
unnamed: U17.5, U$118.1
unnamed: U17.6, U$114.1
unnamed: U17.7, U$115.1
unnamed: U17.2, U$117.1
unnamed: U18.5, U$125.1
unnamed: U18.6, U$121.1
unnamed: U18.7, U$122.1
unnamed: U18.2, U$124.1
unnamed: U19.5, U$132.1
unnamed: U19.6, U$128.1
unnamed: U19.7, U$129.1
unnamed: U19.2, U$131.1
unnamed: U20.5, U$139.1
unnamed: U20.6, U$135.1
unnamed: U20.7, U$136.1
unnamed: U20.2, U$138.1
unnamed: U21.5, U$146.1
unnamed: U21.6, U$142.1
unnamed: U21.7, U$143.1
unnamed: U21.2, U$145.1
unnamed: U22.5, U$153.1
unnamed: U22.6, U$149.1
unnamed: U22.7, U$150.1
unnamed: U22.2, U$152.1
unnamed: U23.5, U$160.1
unnamed: U23.6, U$156.1
unnamed: U23.7, U$157.1
unnamed: U23.2, U$159.1
unnamed: U24.5, U$167.1
unnamed: U24.6, U$163.1
unnamed: U24.7, U$164.1
unnamed: U24.2, U$166.1
unnamed: U25.5, U$174.1
unnamed: U25.6, U$170.1
unnamed: U25.7, U$171.1
unnamed: U25.2, U$173.1
NRESET: R1.2, U1.1
NRESET1: R2.2, U2.1
NRESET2: R3.2, U3.1
NRESET3: R4.2, U4.1
NRESET4: R5.2, U5.1
NRESET5: R6.2, U6.1
NRESET6: R7.2, U7.1
NRESET7: R8.2, U8.1
NRESET8: R9.2, U9.1
NRESET9: R10.2, U10.1
NRESET10: R11.2, U11.1
NRESET11: R12.2, U12.1
NRESET12: R13.2, U13.1
NRESET13: R14.2, U14.1
NRESET14: R15.2, U15.1
NRESET15: R16.2, U16.1
NRESET16: R17.2, U17.1
NRESET17: R18.2, U18.1
NRESET18: R19.2, U19.1
NRESET19: R20.2, U20.1
NRESET20: R21.2, U21.1
NRESET21: R22.2, U22.1
NRESET22: R23.2, U23.1
NRESET23: R24.2, U24.1
NRESET24: R25.2, U25.1
VCC: C1.1, R1.1, U1.8, U$5.1
VCC1: C2.1, R2.1, U2.8, U$11.1
VCC2: C3.1, R3.1, U3.8, U$18.1
VCC3: C4.1, R4.1, U4.8, U$25.1
VCC4: C5.1, R5.1, U5.8, U$32.1
VCC5: C6.1, R6.1, U6.8, U$39.1
VCC6: C7.1, R7.1, U7.8, U$46.1
VCC7: C8.1, R8.1, U8.8, U$53.1
VCC8: C9.1, R9.1, U9.8, U$60.1
VCC9: C10.1, R10.1, U10.8, U$67.1
VCC10: C11.1, R11.1, U11.8, U$74.1
VCC11: C12.1, R12.1, U12.8, U$81.1
VCC12: C13.1, R13.1, U13.8, U$88.1
VCC13: C14.1, R14.1, U14.8, U$95.1
VCC14: C15.1, R15.1, U15.8, U$102.1
VCC15: C16.1, R16.1, U16.8, U$109.1
VCC16: C17.1, R17.1, U17.8, U$116.1
VCC17: C18.1, R18.1, U18.8, U$123.1
VCC18: C19.1, R19.1, U19.8, U$130.1
VCC19: C20.1, R20.1, U20.8, U$137.1
VCC20: C21.1, R21.1, U21.8, U$144.1
VCC21: C22.1, R22.1, U22.8, U$151.1
VCC22: C23.1, R23.1, U23.8, U$158.1
VCC23: C24.1, R24.1, U24.8, U$165.1
VCC24: C25.1, R25.1, U25.8, U$172.1

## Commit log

2012-11-21 Initial commit.
    This is v12 of the board and the shipping firmware as of 21 Nov 2012.
    Going forward changes to board files or firmware will be done through
    Git; older changes persist in SparkFun servers only.
2013-02-14 Added fuse bit strings for AVRDUDE in the code files.
2013-02-26 Added an all-LED twinkle at boot time.
2013-02-26 Added analog input random seed. Made enable comparison boolean.
2013-03-07 porting readme to markdown, adding images, links, and license info, organizing
2013-03-07 fix a poorly worded sentence
2013-03-07 "to write new CODE" ... sentences need subjects.
2013-03-13 Corrected ATtiny capitalization
2013-04-16 Added fritzing parts.
2013-07-31 Adding Firmware tick marks
    After programming firmware, our techs will put a small mark on the
    appropriate box. This is to help ensure that we don't mix the two
    different products up in SFE inventory. A big thanks to meatball for
    instigating this change!!
2013-07-31 Moved components to 0603 package size
2013-07-31 Moved to 0603 components, added OSHW logo
    -moved R1 and C1 a bit to fit in 0603 packages. Had to re-route some
    traces.
    -Added OSHW.
    -Updated Frame.
    -added version to both sch and brd
2014-02-19 Updating license info in README
2014-02-19 Updating production file organization
2014-02-19 Updating files to more clearly differentiate between Tiny/Twinkle
2014-02-19 Correcting hardware files to current pcbs we are selling
2014-03-26 Fixing silk errors from protos
2014-03-27 Fixing merge conflicts
2014-03-27 Fixing merge conflicts numero dos.
    Getting files ready for production runs.
2014-04-02 Added regular fid to board. Deleted old gerbs
2014-04-02 deleted old files
2014-04-02 created panel v12
2014-05-07 Fixed bStop on programming vias
    There is bStop added to expose the bottom side of the programming vias.
    It used to be a circle, which did not expose 100% of the via - it still
    contained a little "dot" of mask covering up the center of the vias.
    This has made it difficult (if not impossible) to program. On this
    commit, I added a circle drawn with the polygon tool to the bStop on all
    6 vias to expose 100% of the vias.
2014-05-08 Switched programming lines from vias to device
    -Used AVR_SPI_PRG_6.dev with the new "TEST_POINTS" package (which
    include the necessary stop mask).
    -Centered symbols in schematic.
2014-05-12 re-did panel v12
2014-06-12 Deleting old pdf of schematic
2021-01-29 Define function for simplicity
    Use a function to reduce code and simplify it
2021-01-29 Correct Fraction
2022-10-09 Coffee mode
    Made a mode where everyone gets excited sometimes.
2022-10-09 Cleanup
    removed some unneeded comments.
2022-10-12 Fast mode random cycle count cleanup
    Added a definition for the minimum and maximum number of fade cycles before a new fast mode cycle.
    Updated the Fast Mode completion routine to use the new fade cycle min/max definitions
2022-10-13 Stylistic changes
    Removing extra white space.
2022-10-13 Celebration mode changes. Fast mode change.
    Refined celebration mode. Ensured that all LEDs reset their fade counters and fade to max brightness.
    Changed how fast mode enables so that LEDs join in for the coffee when ever they're ready, instead of mid-way through a fade.
2022-10-13 Comment cleanup
    cleaned up extra comments.
2022-10-13 Array experiment
    Experimenting with replacing sequentially numbered variables of many values for each LED with arrays.
    Initialized fadeTimer as an array. Replaced all instances of fadeTimerX with it's associated array.
2022-10-13 Loop implementation
    Instead of manually setting the value for each LED's fadeTimerX variable, loop over each using an array.
2022-10-13 Converted onTimeX to arrays
2022-10-13 Updated celebration for loop
    Added onTime[] array to the celebration loop that resets everyone's fade.
2022-10-13 Typo correction
    Correcting missed variable during last array conversion
2022-10-13 Array-ifying
2022-10-13 Final array-ification edits
    added a for loop to the coffee-enable conditional.
2022-10-18 Formatting: ArduinoIDE
2022-10-18 Fixes
    Line 103, boolean conditional test shorthand.
2025-06-27 Update README.md
    Updating link

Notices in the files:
parts and their libraries:
SparkFun-Aesthetics: Licensing: CC v3.0 Share-Alike You are welcome to use this library for commercial purposes.
SparkFun-Aesthetics: Released under the Creative Commons Attribution Share-Alike 4.0 License
SparkFun-Aesthetics: Released under the Creative Commons
